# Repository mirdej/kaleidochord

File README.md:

# Kaleidochord
the kaleidochord (aka videoscheitholt or videozither) is a visual instrument that combines the videobass with the vmix

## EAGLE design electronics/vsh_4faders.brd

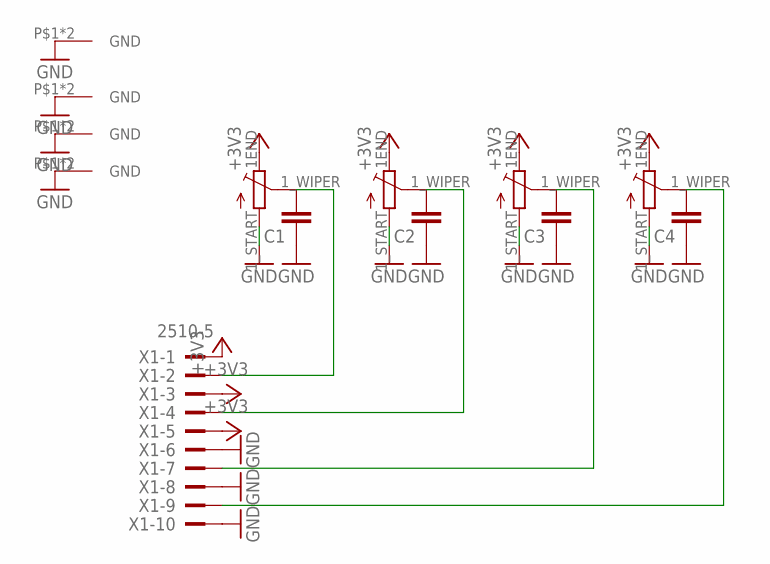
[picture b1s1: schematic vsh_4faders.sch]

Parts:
C1, C2, C3, C4: C-EUC0603; C0603
U$1, U$2, U$3, U$5: ALPS_FADER_MONO; ALPS_FADER_60MM_MONO
X1: 2510-5; PAK100/2500-5-10

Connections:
+3V3: U$1.1END (ENDE), U$2.1END (ENDE), U$3.1END (ENDE), U$5.1END (ENDE), X1.1, X1.3, X1.5
GND: C1.1, C2.1, C3.1, C4.1, U$1.1_START (ANFANG), U$1.P$1 (GND), U$1.P$2 (GND), U$2.1_START (ANFANG), U$2.P$1 (GND), U$2.P$2 (GND), U$3.1_START (ANFANG), U$3.P$1 (GND), U$3.P$2 (GND), U$5.1_START (ANFANG), U$5.P$1 (GND), U$5.P$2 (GND), X1.6, X1.8, X1.10
unnamed: C2.2, U$1.1_WIPER (SCHLEIFER), X1.4
unnamed: C1.2, U$5.1_WIPER (SCHLEIFER), X1.2
unnamed: C4.2, U$3.1_WIPER (SCHLEIFER), X1.9
unnamed: C3.2, U$2.1_WIPER (SCHLEIFER), X1.7

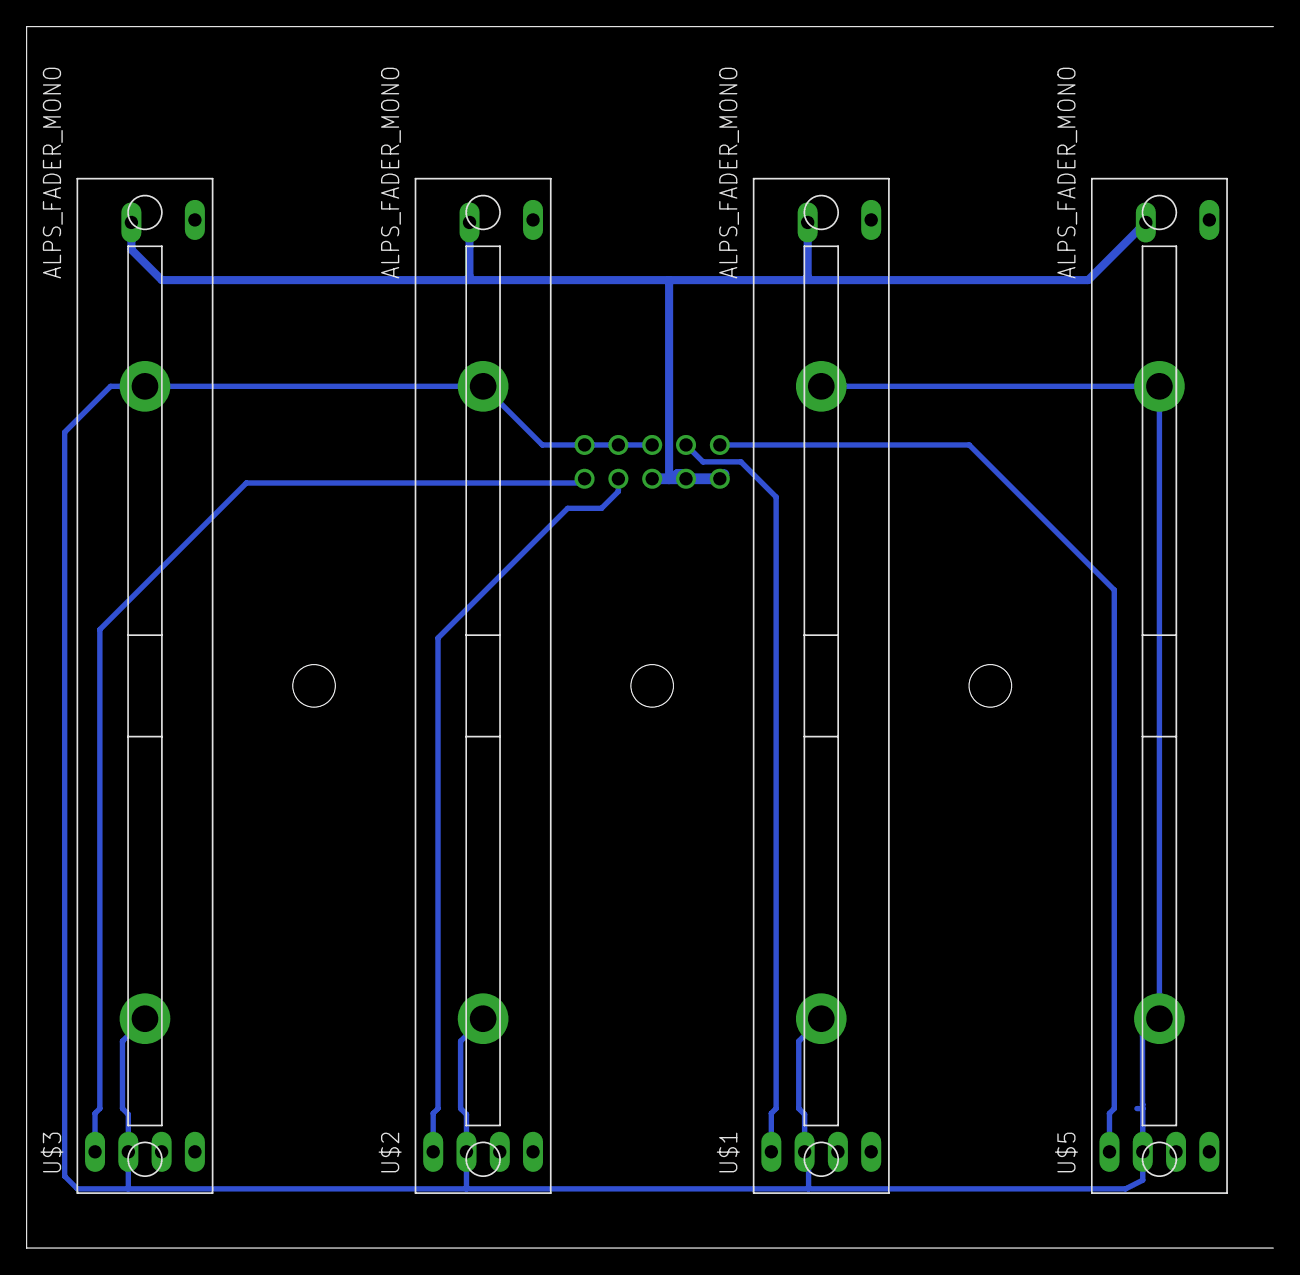
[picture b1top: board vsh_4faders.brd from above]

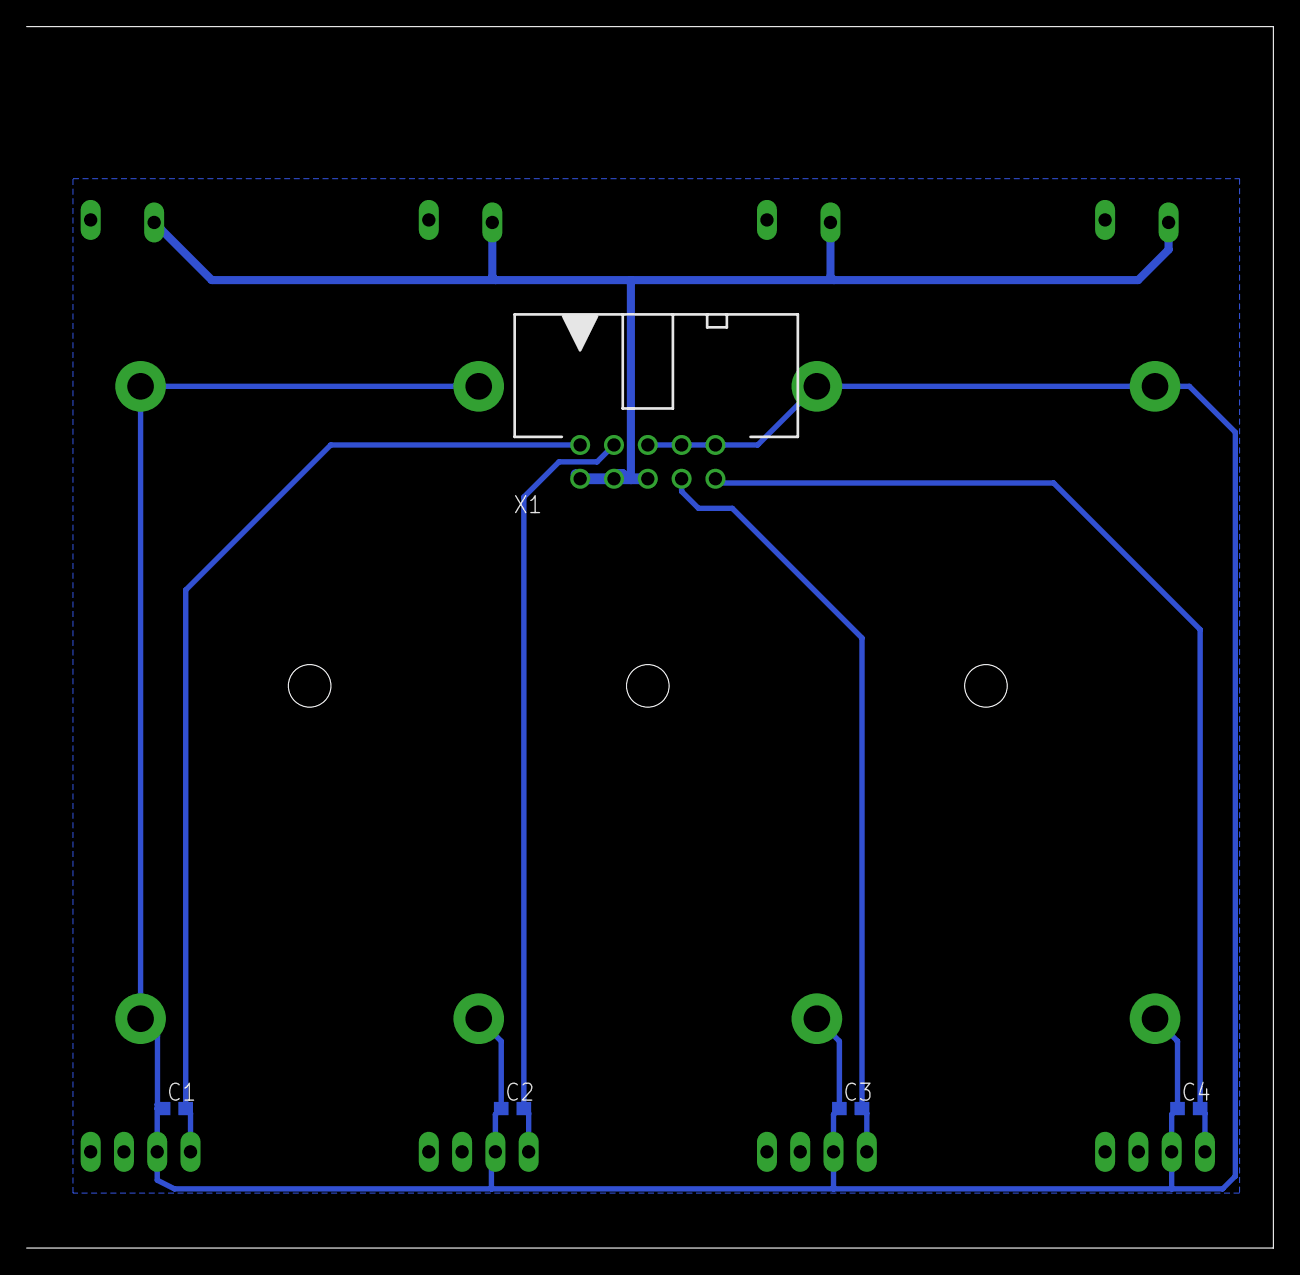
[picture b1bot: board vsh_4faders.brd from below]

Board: 2 copper layers, 93.6 x 91.7 mm, 9 parts (5 on the bottom side), 6 nets.

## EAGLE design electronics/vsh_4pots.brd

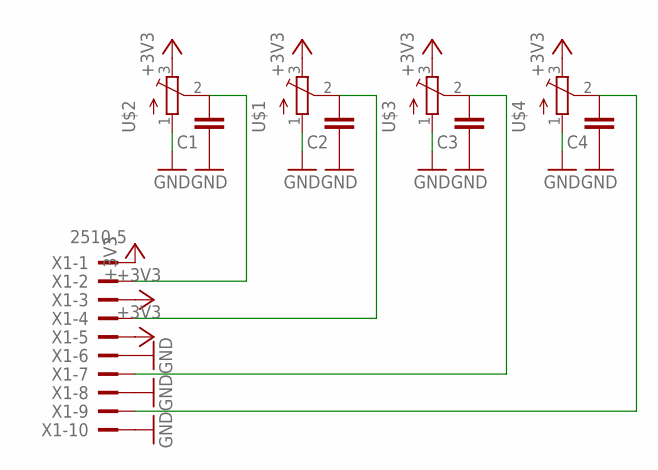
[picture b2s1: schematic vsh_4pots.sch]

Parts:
C1, C2, C3, C4: C-EUC0603; C0603
U$1, U$2, U$3, U$4: ALPS_RK09K111_H09L1120; ALPS_RK09L1120
X1: 2510-5; PAK100/2500-5-10

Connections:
+3V3: U$1.3 (E), U$2.3 (E), U$3.3 (E), U$4.3 (E), X1.1, X1.3, X1.5
GND: C1.1, C2.1, C3.1, C4.1, U$1.1 (S), U$2.1 (S), U$3.1 (S), U$4.1 (S), X1.6, X1.8, X1.10
unnamed: C2.2, U$1.2 (W), X1.4
unnamed: C1.2, U$2.2 (W), X1.2
unnamed: C4.2, U$4.2 (W), X1.9
unnamed: C3.2, U$3.2 (W), X1.7

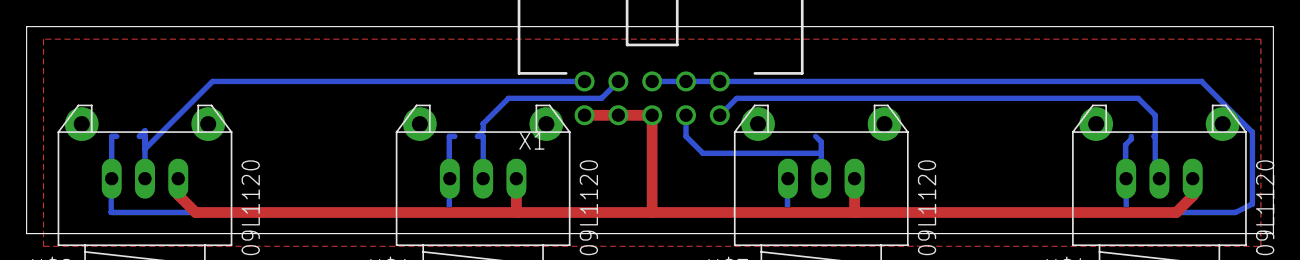
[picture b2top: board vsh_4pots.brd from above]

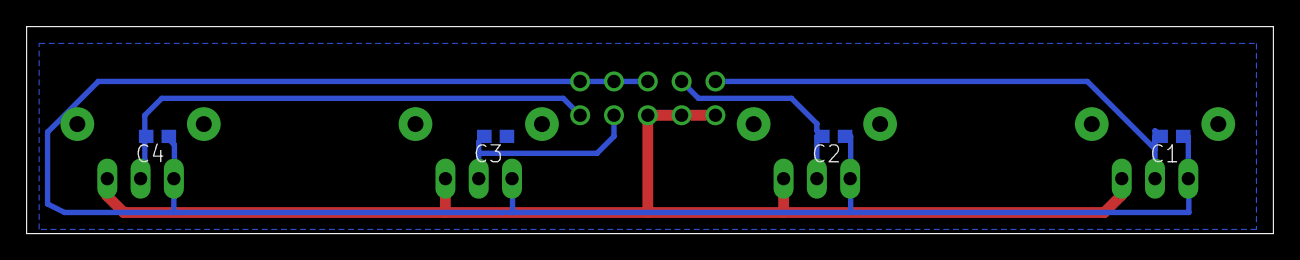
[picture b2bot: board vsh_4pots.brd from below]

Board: 2 copper layers, 93.6 x 15.5 mm, 9 parts (4 on the bottom side), 6 nets.

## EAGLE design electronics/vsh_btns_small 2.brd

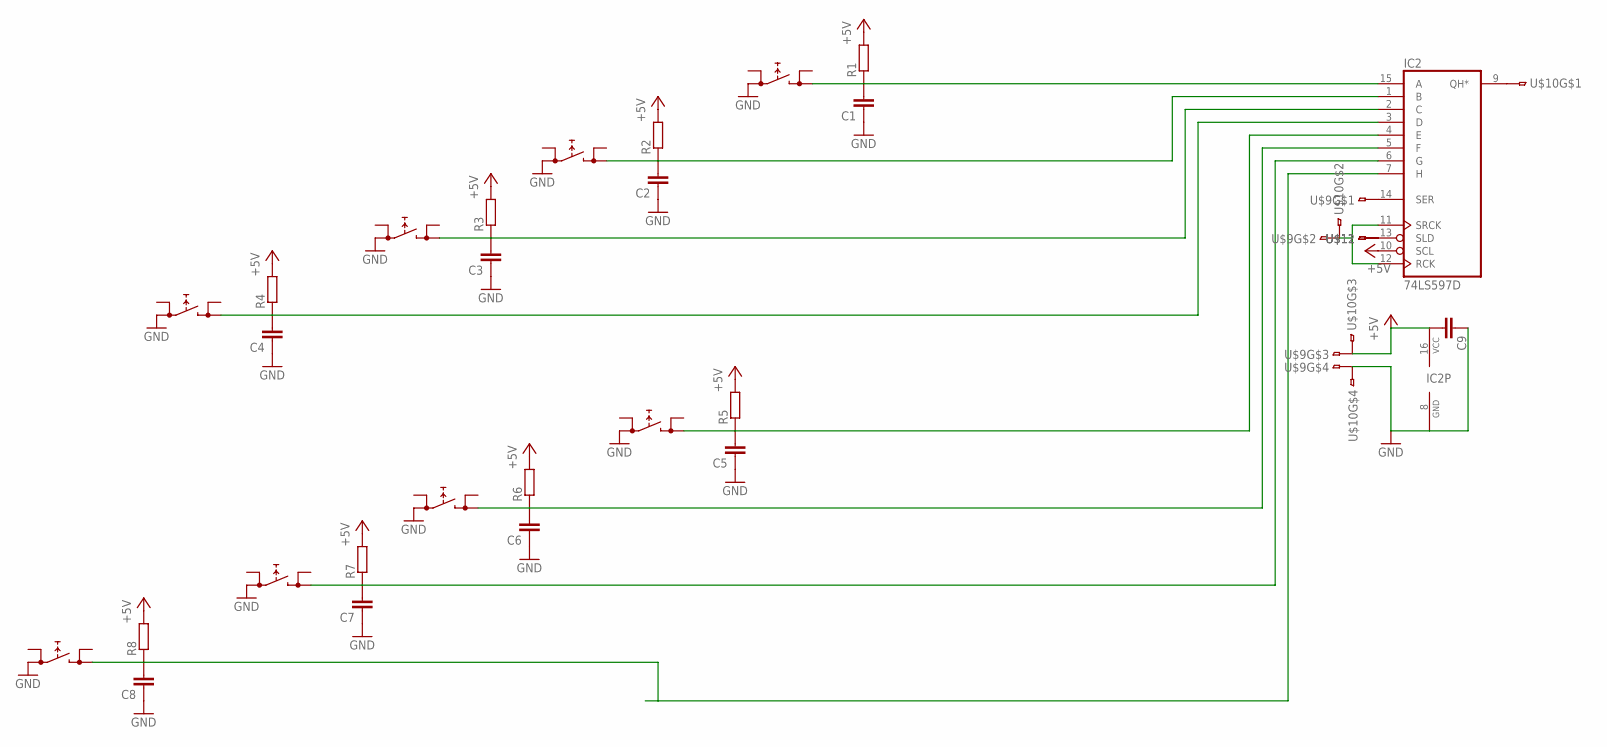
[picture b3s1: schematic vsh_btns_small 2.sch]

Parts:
C1, C2, C3, C4, C5, C6, C7, C8, C9: C-EUC1206; C1206
IC2: 74LS597D; SO16
R1, R2, R3, R4, R5, R6, R7, R8: R-EU_R1206; R1206
U$1, U$2, U$3, U$4, U$5, U$6, U$7, U$8: PRINTTASTER_SMDALPS-SKQ; SKQGAKE010
U$9, U$10: 4PIN-SMD; 4PIN-SMD-2.54
U$11, U$12: 1PINSMD

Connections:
+5V: C9.2, IC2.10 (SCL), IC2.16 (VCC), R1.2, R2.2, R3.2, R4.2, R5.2, R6.2, R7.2, R8.2, U$9.3, U$10.3
GND: C1.1, C2.1, C3.1, C4.1, C5.1, C6.1, C7.1, C8.1, C9.1, IC2.8 (GND), U$1.2 (0), U$2.2 (0), U$3.2 (0), U$4.2 (0), U$5.2 (0), U$6.2 (0), U$7.2 (0), U$8.2 (0), U$9.4, U$10.4
MISO: IC2.9 (QH*), U$10.1
unnamed: C1.2, IC2.15 (A), R1.1, U$1.4 (1)
unnamed: C2.2, IC2.1 (B), R2.1, U$2.4 (1)
unnamed: C3.2, IC2.2 (C), R3.1, U$3.4 (1)
unnamed: C4.2, IC2.3 (D), R4.1, U$4.4 (1)
unnamed: C5.2, IC2.4 (E), R5.1, U$5.4 (1)
unnamed: C6.2, IC2.5 (F), R6.1, U$6.4 (1)
unnamed: C7.2, IC2.6 (G), R7.1, U$7.4 (1)
unnamed: IC2.14 (SER), U$9.1
unnamed: IC2.11 (SRCK), IC2.12 (RCK), U$9.2, U$10.2
unnamed: C8.2, IC2.7 (H), R8.1, U$8.4 (1)
unnamed: IC2.13 (SLD), U$11.2, U$12.2

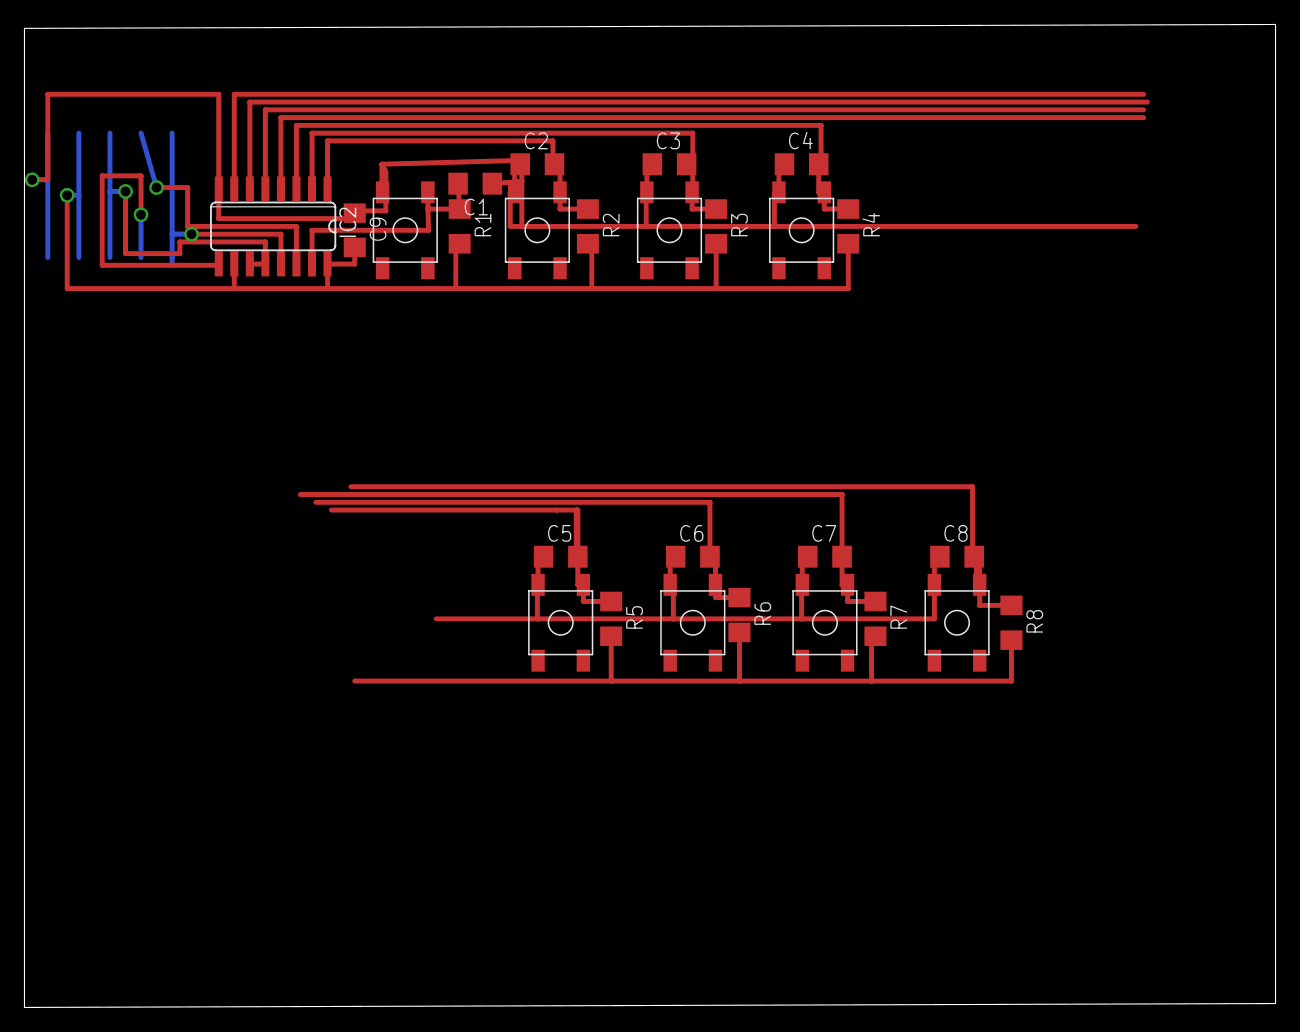
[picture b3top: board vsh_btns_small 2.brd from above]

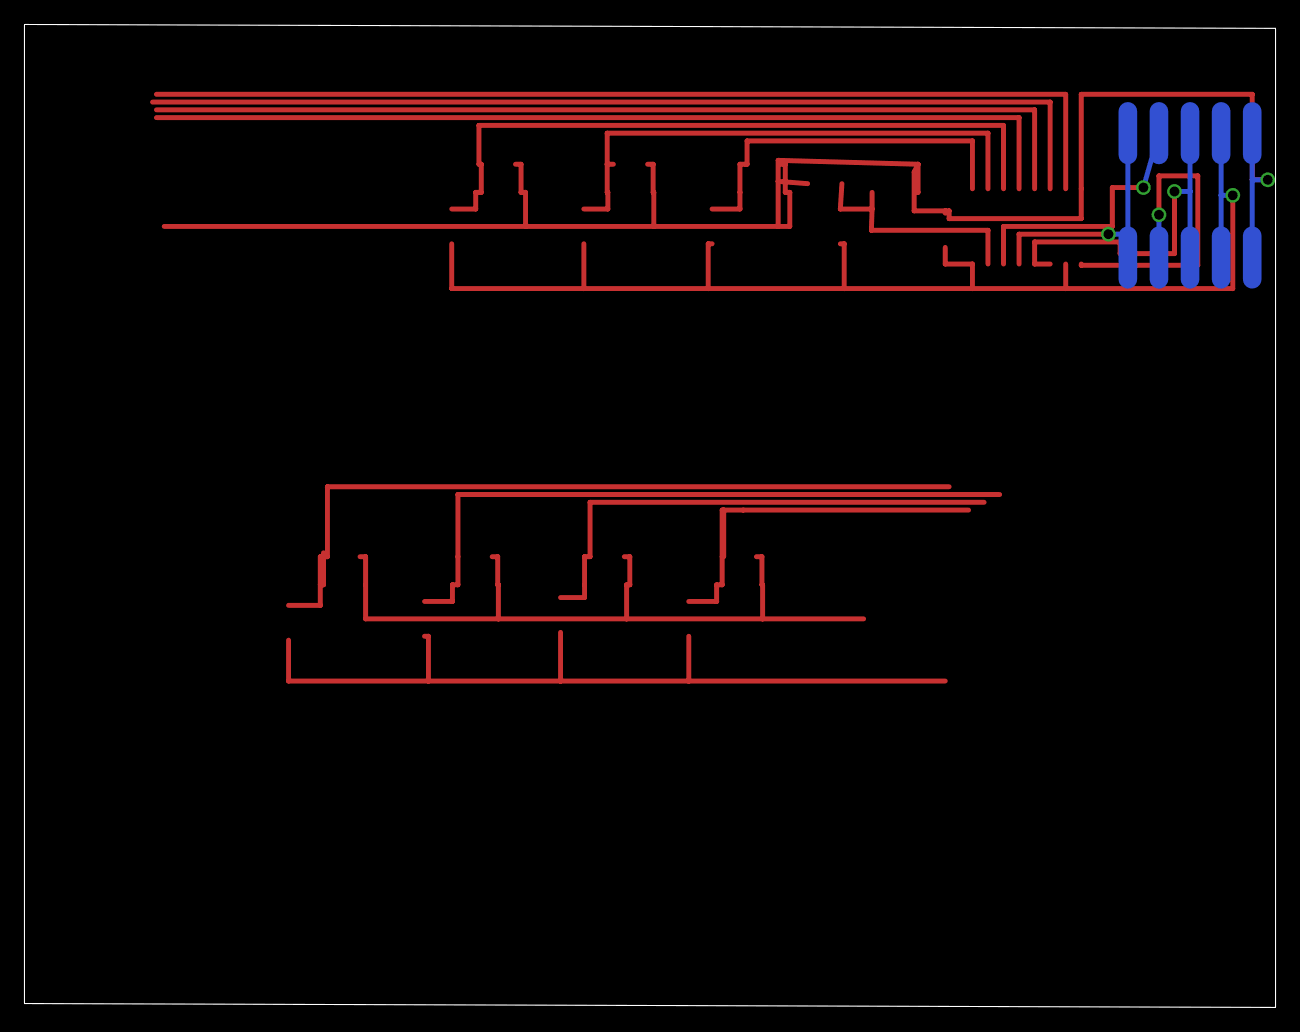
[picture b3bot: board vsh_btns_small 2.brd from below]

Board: 2 copper layers, 102.2 x 80.3 mm, 30 parts (4 on the bottom side), 14 nets.

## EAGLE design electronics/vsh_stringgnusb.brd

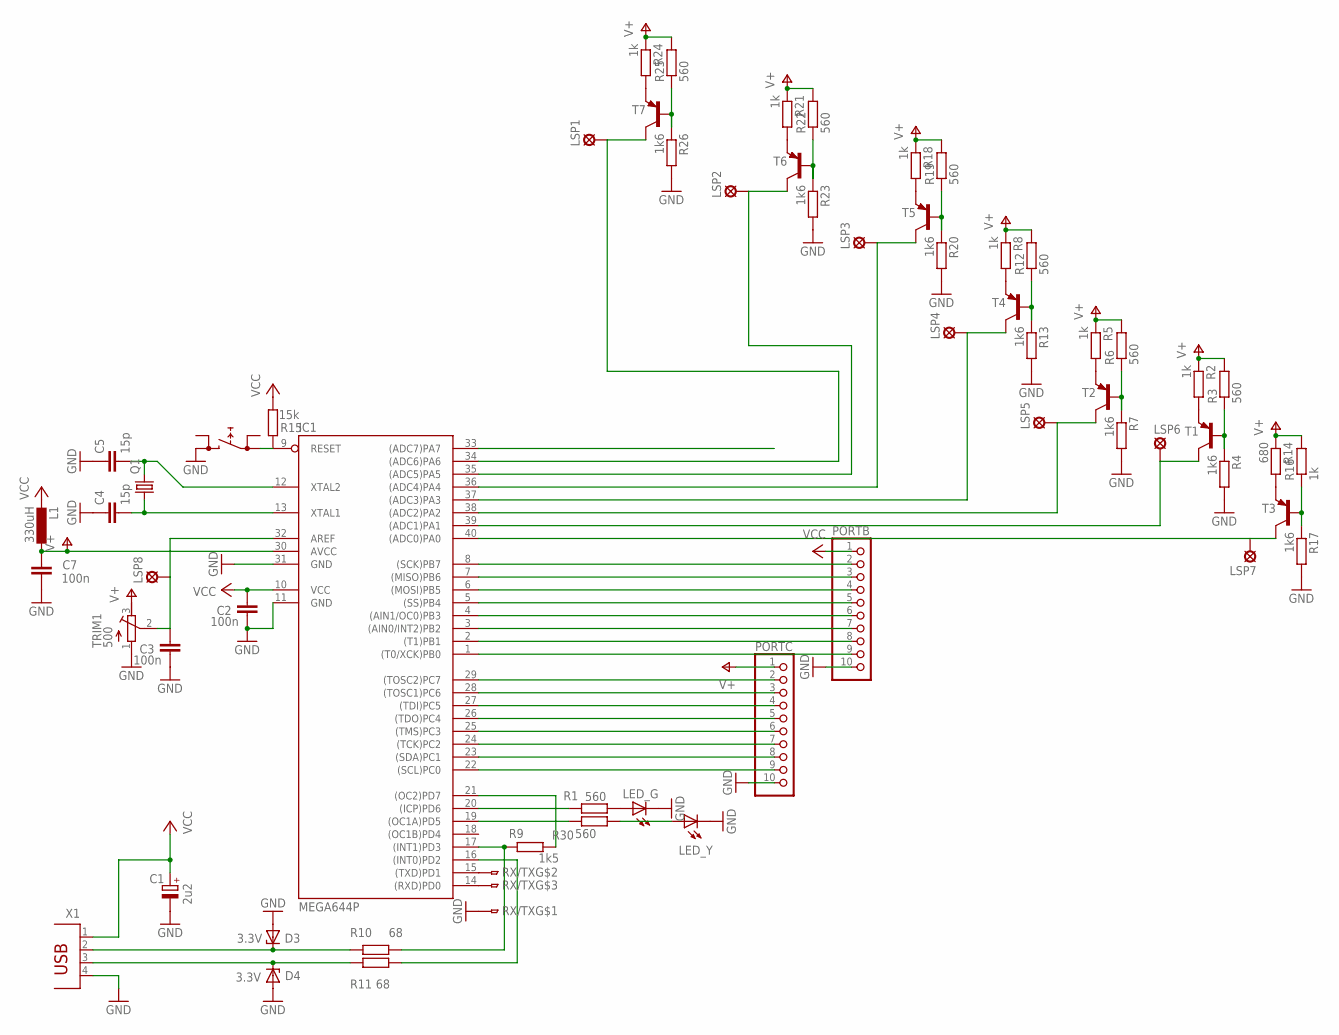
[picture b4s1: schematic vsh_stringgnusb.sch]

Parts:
C1: 2u2; CT3528
C2, C7: 100n; C0805
C3: 100n; C1206
C4, C5: 15p; C1206
D3, D4: 3.3V; SOD80C
IC1: MEGA644P; DIL40
L1: 330uH; L1812
LED_G: LEDCHIPLED_1206; CHIPLED_1206
LED_Y: LEDCHIPLED_1206; CHIPLED_1206
LSP1, LSP2, LSP3, LSP4, LSP5, LSP6, LSP7, LSP8: LSP11
PORTB: 10-PIN-SMD-2.54; 10PIN-SMD-2.54
PORTC: 10-PIN-SMD-2.54; 10PIN-SMD-2.54
Q1: CRYSTALHC49UP; HC49UP
R1, R30: 560; M1206
R2, R5, R8, R16, R18, R21, R24: 1k; R1206
R3, R6, R12, R19, R22, R25: 560; R1206
R4, R7, R13, R17, R20, R23, R26: 1k6; R1206
R9: 1k5; M1206
R10, R11: 68; M1206
R14: 680; R1206
R15: 15k; M1206
RESET: PRINTTASTER_SMD; SMD_SWITCH
RX/TX: 3PIN-SMD-2.54
T1, T2, T3, T4, T5, T6, T7: -PNP-SOT23-BCE; SOT23-BCE
TRIM1: 500; RTRIM64Y
X1: PN61729

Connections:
D+: D4.C, R11.1, X1.3
D-: D3.C, R10.1, X1.2
GND: C1.-, C2.2, C3.2, C4.1, C5.1, C7.2, D3.A, D4.A, IC1.11 (GND), IC1.31 (GND), LED_G.C, LED_Y.C, PORTB.10, PORTC.10, R4.2, R7.2, R13.2, R17.2, R20.2, R23.2, R26.2, RESET.BB (1), RX/TX.1, TRIM1.1 (E), X1.4
MISO: IC1.7 ((MISO)PB6), PORTB.3
MOSI: IC1.6 ((MOSI)PB5), PORTB.4
unnamed: IC1.17 ((INT1)PD3), R9.2, R10.2
unnamed: IC1.9 (RESET), R15.1, RESET.AA (0)
unnamed: IC1.15 ((TXD)PD1), RX/TX.2
unnamed: IC1.14 ((RXD)PD0), RX/TX.3
unnamed: LED_G.A, R1.2
unnamed: C4.2, IC1.13 (XTAL1), Q1.1
unnamed: IC1.20 ((ICP)PD6), R1.1
unnamed: IC1.19 ((OC1A)PD5), R30.1
unnamed: LED_Y.A, R30.2
unnamed: R14.2, T3.E
unnamed: C3.1, IC1.32 (AREF), LSP8.MP, TRIM1.2 (S)
unnamed: IC1.21 ((OC2)PD7), R9.1
unnamed: R2.2, T1.E
unnamed: IC1.35 ((ADC5)PA5), LSP2.MP, T6.C
unnamed: IC1.37 ((ADC3)PA3), LSP4.MP, T4.C
unnamed: IC1.38 ((ADC2)PA2), LSP5.MP, T2.C
unnamed: IC1.40 ((ADC0)PA0), LSP7.MP, T3.C
unnamed: R16.1, R17.1, T3.B
unnamed: IC1.4 ((AIN1/OC0)PB3), PORTB.6
unnamed: IC1.3 ((AIN0/INT2)PB2), PORTB.7
unnamed: IC1.2 ((T1)PB1), PORTB.8
unnamed: IC1.1 ((T0/XCK)PB0), PORTB.9
unnamed: IC1.16 ((INT0)PD2), R11.2
unnamed: IC1.29 ((TOSC2)PC7), PORTC.2
unnamed: IC1.28 ((TOSC1)PC6), PORTC.3
unnamed: IC1.27 ((TDI)PC5), PORTC.4
unnamed: IC1.26 ((TDO)PC4), PORTC.5
unnamed: IC1.25 ((TMS)PC3), PORTC.6
unnamed: IC1.24 ((TCK)PC2), PORTC.7
unnamed: IC1.23 ((SDA)PC1), PORTC.8
unnamed: IC1.22 ((SCL)PC0), PORTC.9
unnamed: IC1.39 ((ADC1)PA1), LSP6.MP, T1.C
unnamed: R3.1, R4.1, T1.B
unnamed: C5.2, IC1.12 (XTAL2), Q1.2
unnamed: R5.2, T2.E
unnamed: R6.1, R7.1, T2.B
unnamed: R8.2, T4.E
unnamed: R12.1, R13.1, T4.B
unnamed: R18.2, T5.E
unnamed: IC1.36 ((ADC4)PA4), LSP3.MP, T5.C
unnamed: R19.1, R20.1, T5.B
unnamed: R21.2, T6.E
unnamed: R22.1, R23.1, T6.B
unnamed: R24.2, T7.E
unnamed: IC1.34 ((ADC6)PA6), LSP1.MP, T7.C
unnamed: R25.1, R26.1, T7.B
SCK: IC1.8 ((SCK)PB7), PORTB.2
SS: IC1.5 ((SS)PB4), PORTB.5
V+: C7.1, IC1.30 (AVCC), L1.1, PORTC.1, R2.1, R3.2, R5.1, R6.2, R8.1, R12.2, R14.1, R16.2, R18.1, R19.2, R21.1, R22.2, R24.1, R25.2, TRIM1.3 (A)
VCC: C1.+, C2.1, IC1.10 (VCC), L1.2, PORTB.1, R15.2, X1.1

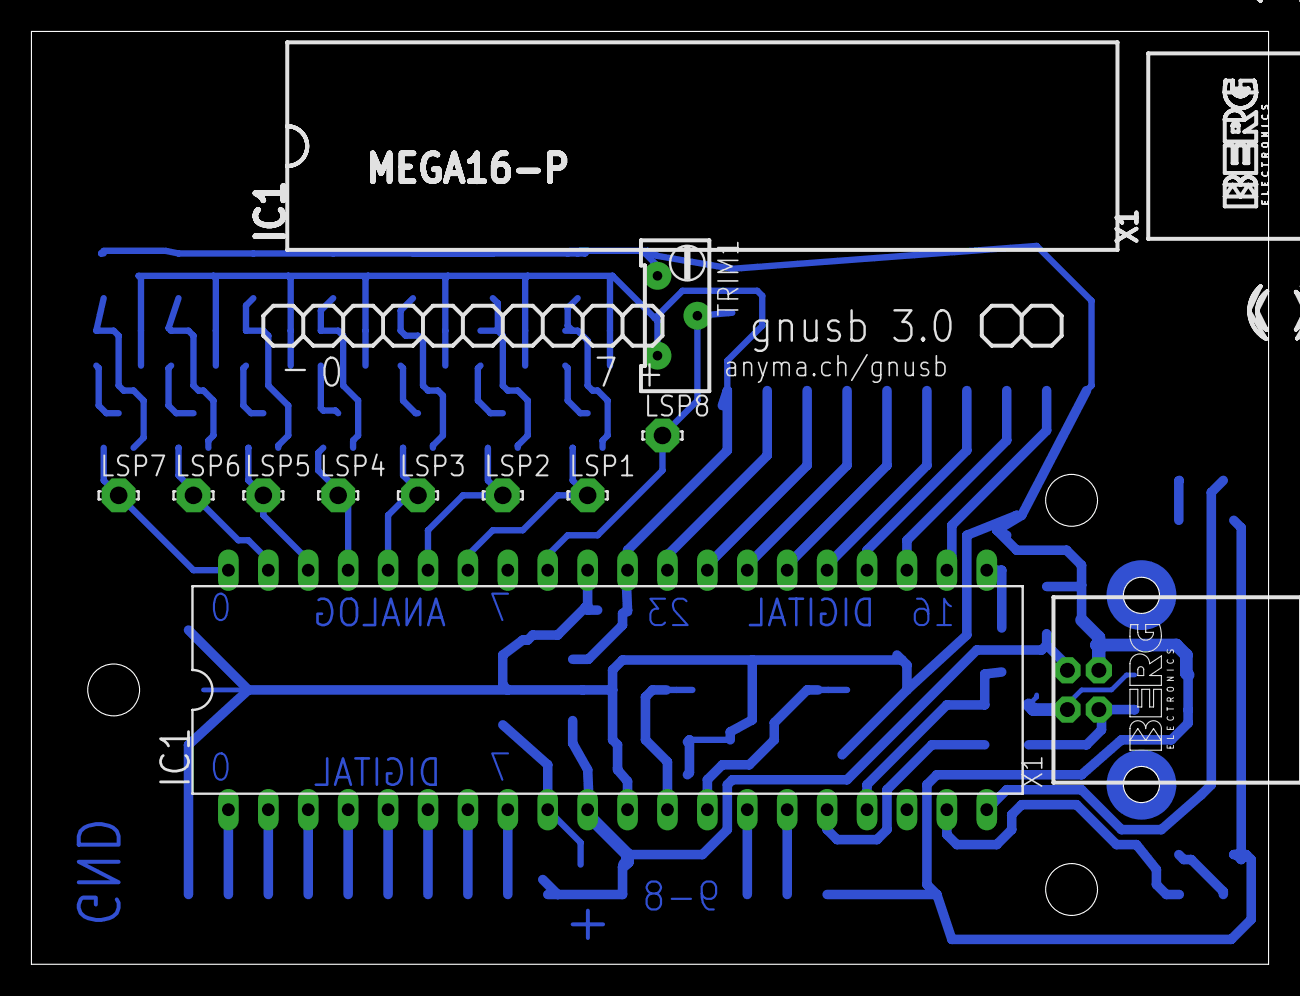
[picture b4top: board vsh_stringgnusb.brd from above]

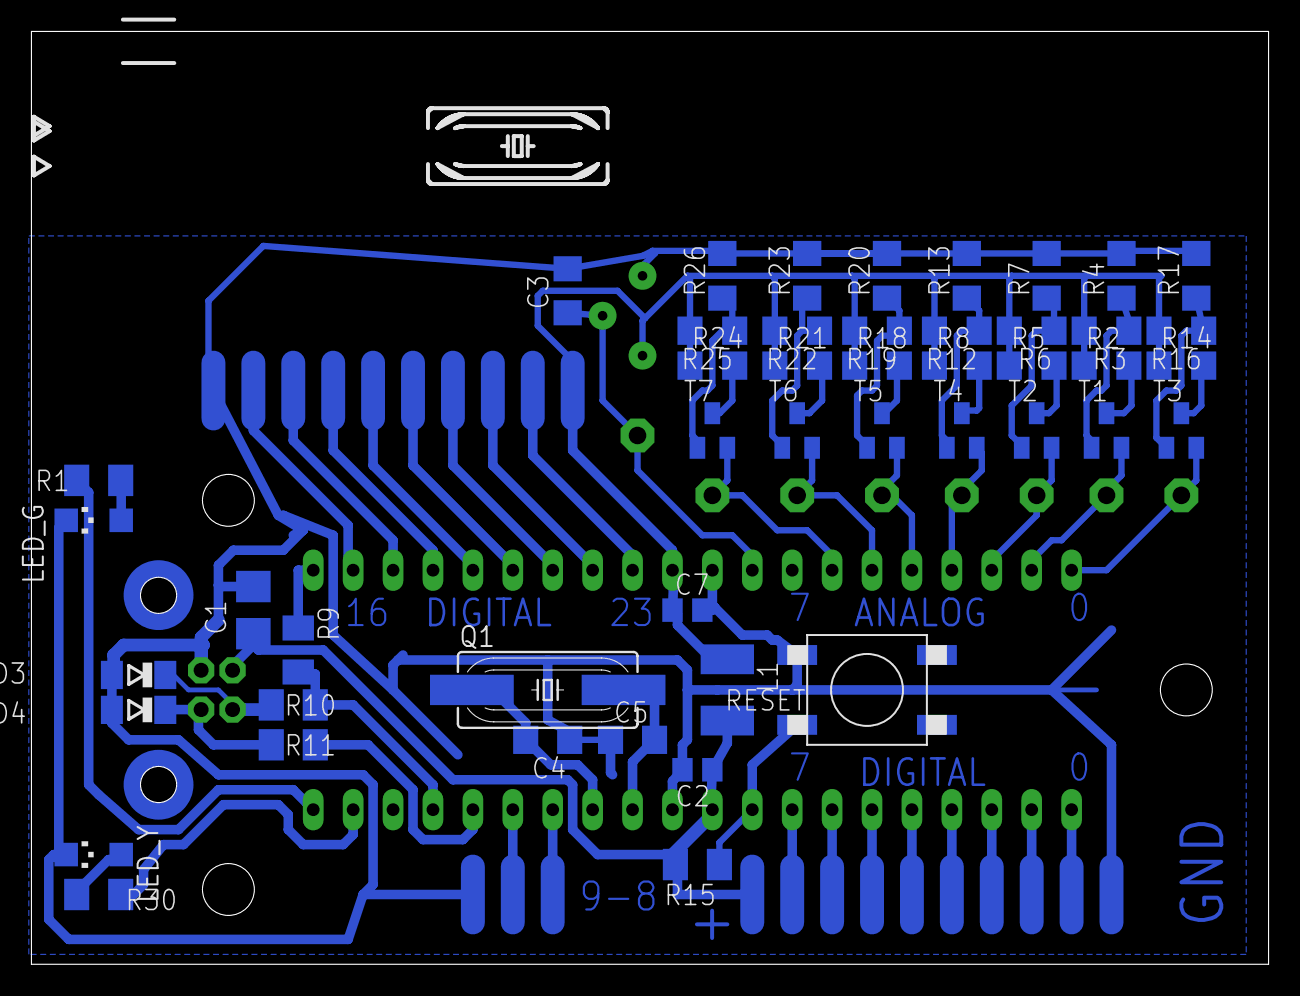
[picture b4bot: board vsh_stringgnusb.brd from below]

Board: 2 copper layers, 78.7 x 59.4 mm, 61 parts (50 on the bottom side), 55 nets.

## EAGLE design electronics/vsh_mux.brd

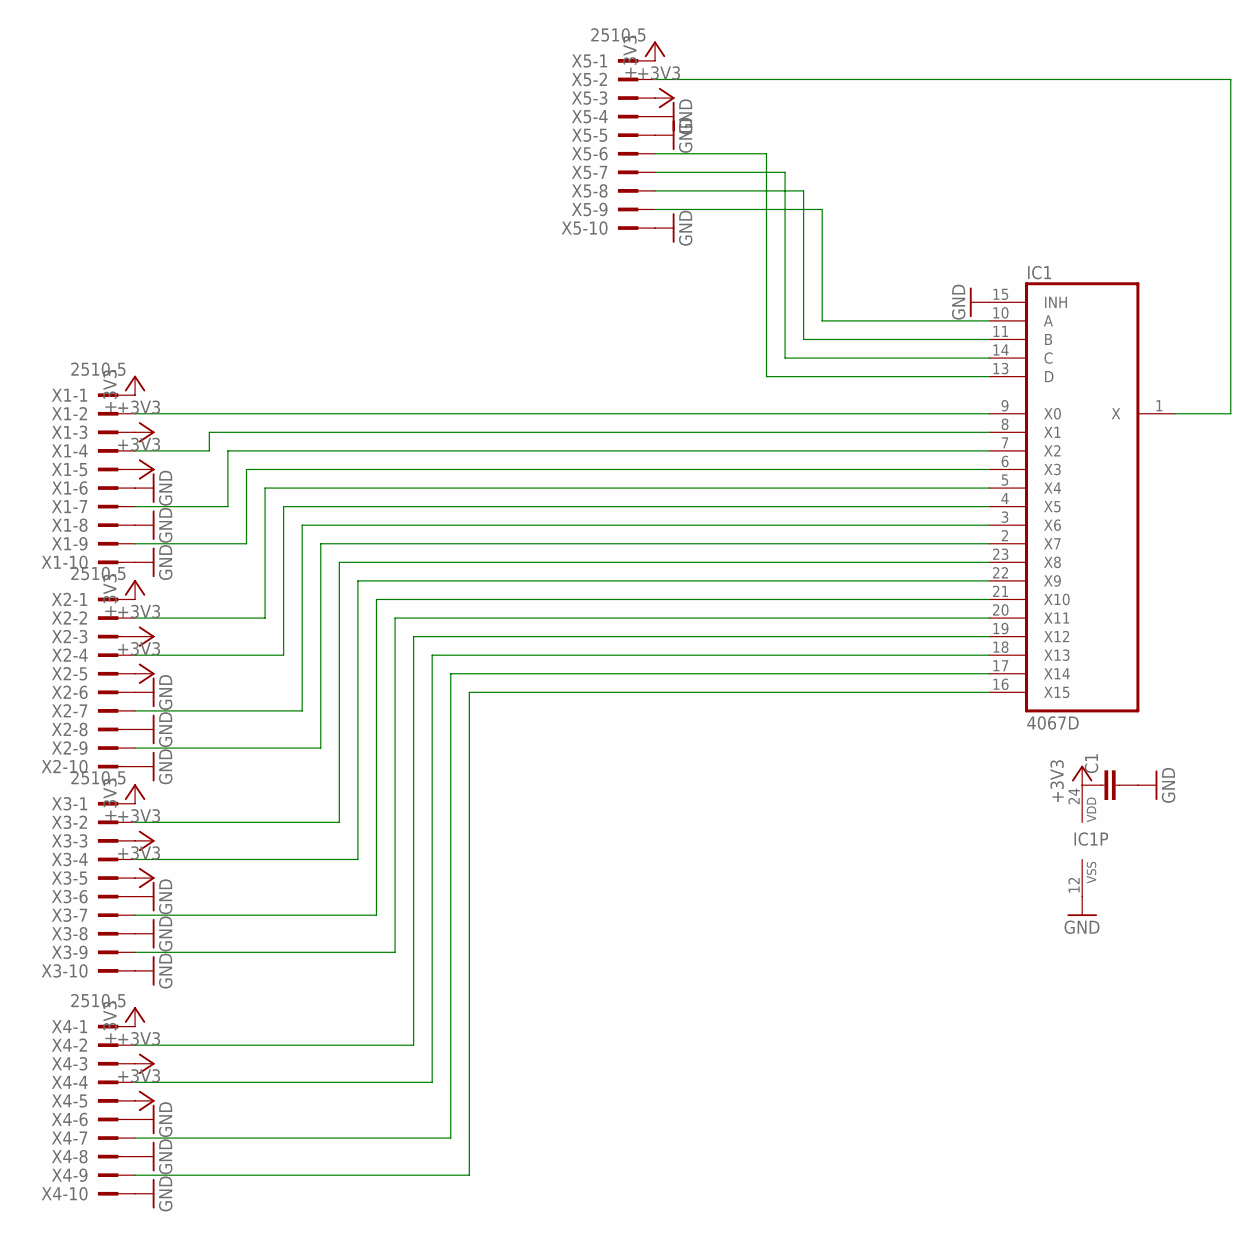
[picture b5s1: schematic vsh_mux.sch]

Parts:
C1: C-EUC1206; C1206
IC1: 4067D; SO24W
X1, X2, X3, X4, X5: 2510-5; PAK100/2500-5-10

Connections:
+3V3: C1.1, IC1.24 (VDD), X1.1, X1.3, X1.5, X2.1, X2.3, X2.5, X3.1, X3.3, X3.5, X4.1, X4.3, X4.5, X5.1, X5.3
GND: C1.2, IC1.12 (VSS), IC1.15 (INH), X1.6, X1.8, X1.10, X2.6, X2.8, X2.10, X3.6, X3.8, X3.10, X4.6, X4.8, X4.10, X5.4, X5.5, X5.10
unnamed: IC1.4 (X5), X2.4
unnamed: IC1.8 (X1), X1.4
unnamed: IC1.1 (X), X5.2
unnamed: IC1.9 (X0), X1.2
unnamed: IC1.6 (X3), X1.9
unnamed: IC1.2 (X7), X2.9
unnamed: IC1.7 (X2), X1.7
unnamed: IC1.3 (X6), X2.7
unnamed: IC1.22 (X9), X3.4
unnamed: IC1.23 (X8), X3.2
unnamed: IC1.20 (X11), X3.9
unnamed: IC1.21 (X10), X3.7
unnamed: IC1.18 (X13), X4.4
unnamed: IC1.10 (A), X5.9
unnamed: IC1.16 (X15), X4.9
unnamed: IC1.17 (X14), X4.7
unnamed: IC1.5 (X4), X2.2
unnamed: IC1.19 (X12), X4.2
unnamed: IC1.11 (B), X5.8
unnamed: IC1.13 (D), X5.6
unnamed: IC1.14 (C), X5.7

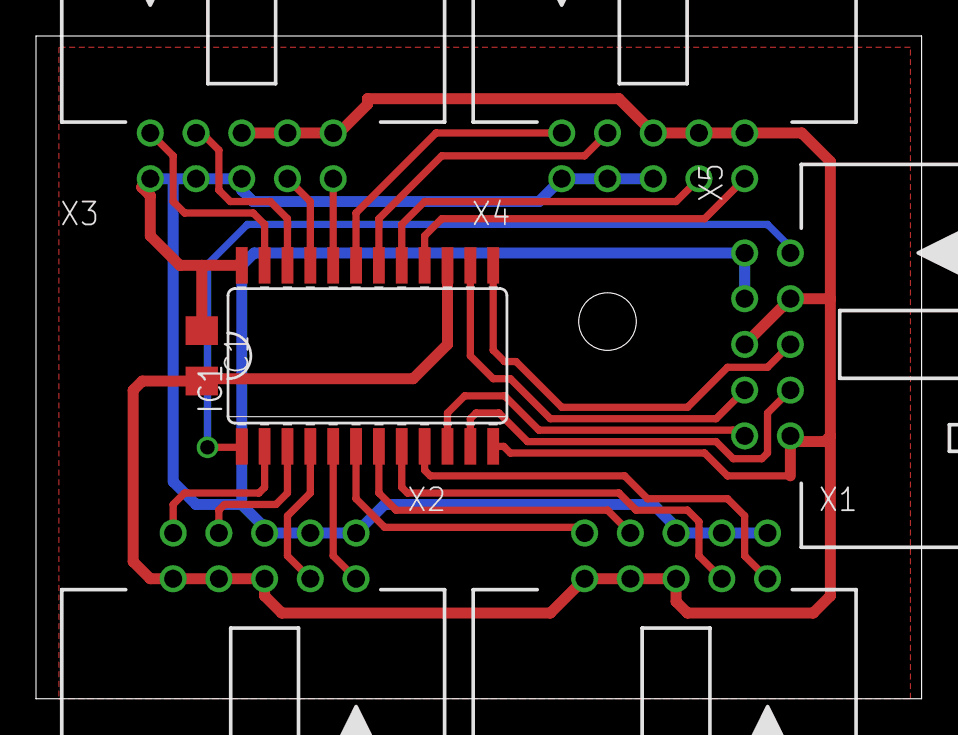
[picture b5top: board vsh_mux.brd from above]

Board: 2 copper layers, 49.2 x 36.8 mm, 7 parts (0 on the bottom side), 23 nets.

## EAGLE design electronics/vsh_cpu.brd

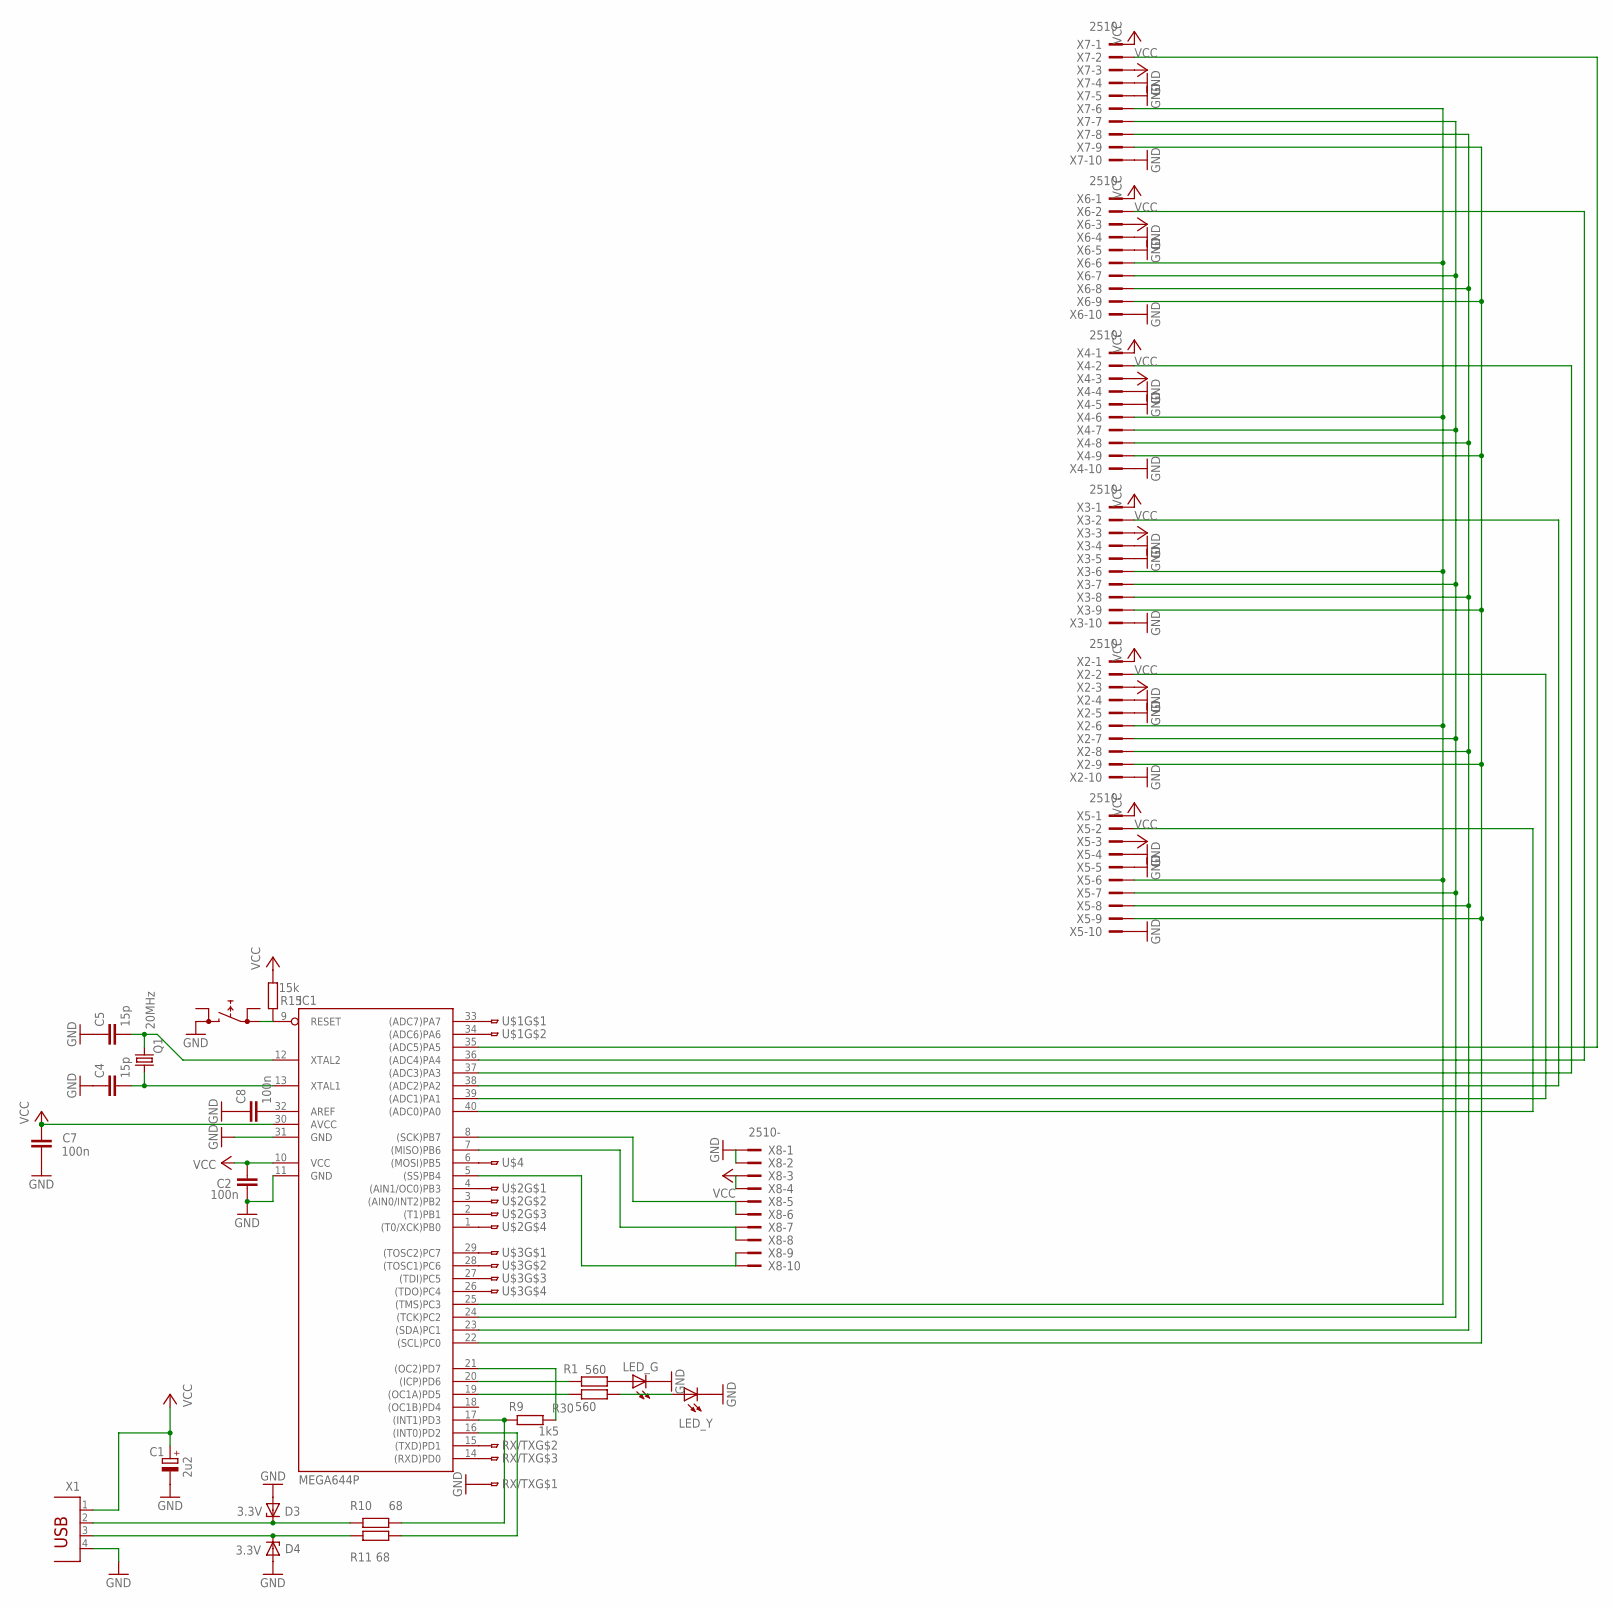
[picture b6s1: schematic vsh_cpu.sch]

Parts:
C1: 2u2; CT3528
C2, C7, C8: 100n; C0805
C4, C5: 15p; C1206
D3, D4: 3.3V; SOD80C
IC1: MEGA644P; DIL40
LED_G: LEDCHIPLED_1206; CHIPLED_1206
LED_Y: LEDCHIPLED_1206; CHIPLED_1206
Q1: 20MHz; HC49UP
R1, R30: 560; M1206
R9: 1k5; M1206
R10, R11: 68; M1206
R15: 15k; M1206
RESET: PRINTTASTER_SMD; SMD_SWITCH
RX/TX: 3PIN-SMD-2.54
U$1: 2PIN-SMD-2.54
U$2, U$3: 4PIN-SMD; 4PIN-SMD-2.54
U$4: 1PINSMD
X1: PN61729
X2, X3, X4, X5, X6, X7, X8: 2510-; PAK100/2500-10

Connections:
D+: D4.C, R11.1, X1.3
D-: D3.C, R10.1, X1.2
GND: C1.-, C2.2, C4.1, C5.1, C7.2, C8.1, D3.A, D4.A, IC1.11 (GND), IC1.31 (GND), LED_G.C, LED_Y.C, RESET.BB (1), RX/TX.1, X1.4, X2.4, X2.5, X2.10, X3.4, X3.5, X3.10, X4.4, X4.5, X4.10, X5.4, X5.5, X5.10, X6.4, X6.5, X6.10, X7.4, X7.5, X7.10, X8.1, X8.2
unnamed: IC1.17 ((INT1)PD3), R9.2, R10.2
unnamed: IC1.9 (RESET), R15.1, RESET.AA (0)
unnamed: IC1.15 ((TXD)PD1), RX/TX.2
unnamed: IC1.14 ((RXD)PD0), RX/TX.3
unnamed: LED_G.A, R1.2
unnamed: C4.2, IC1.13 (XTAL1), Q1.1
unnamed: IC1.20 ((ICP)PD6), R1.1
unnamed: IC1.19 ((OC1A)PD5), R30.1
unnamed: LED_Y.A, R30.2
unnamed: IC1.40 ((ADC0)PA0), X5.2
unnamed: C8.2, IC1.32 (AREF)
unnamed: IC1.39 ((ADC1)PA1), X2.2
unnamed: IC1.21 ((OC2)PD7), R9.1
unnamed: IC1.38 ((ADC2)PA2), X3.2
unnamed: IC1.25 ((TMS)PC3), X2.6, X3.6, X4.6, X5.6, X6.6, X7.6
unnamed: IC1.33 ((ADC7)PA7), U$1.2
unnamed: IC1.24 ((TCK)PC2), X2.7, X3.7, X4.7, X5.7, X6.7, X7.7
unnamed: IC1.34 ((ADC6)PA6), U$1.3
unnamed: IC1.23 ((SDA)PC1), X2.8, X3.8, X4.8, X5.8, X6.8, X7.8
unnamed: IC1.8 ((SCK)PB7), X8.5, X8.6
unnamed: IC1.37 ((ADC3)PA3), X4.2
unnamed: IC1.36 ((ADC4)PA4), X6.2
unnamed: IC1.7 ((MISO)PB6), X8.7, X8.8
unnamed: IC1.5 ((SS)PB4), X8.9, X8.10
unnamed: IC1.16 ((INT0)PD2), R11.2
unnamed: IC1.22 ((SCL)PC0), X2.9, X3.9, X4.9, X5.9, X6.9, X7.9
unnamed: IC1.35 ((ADC5)PA5), X7.2
unnamed: IC1.4 ((AIN1/OC0)PB3), U$2.1
unnamed: IC1.3 ((AIN0/INT2)PB2), U$2.2
unnamed: IC1.2 ((T1)PB1), U$2.3
unnamed: IC1.29 ((TOSC2)PC7), U$3.1
unnamed: IC1.28 ((TOSC1)PC6), U$3.2
unnamed: IC1.27 ((TDI)PC5), U$3.3
unnamed: IC1.26 ((TDO)PC4), U$3.4
unnamed: C5.2, IC1.12 (XTAL2), Q1.2
unnamed: IC1.1 ((T0/XCK)PB0), U$2.4
unnamed: IC1.6 ((MOSI)PB5), U$4.2
VCC: C1.+, C2.1, C7.1, IC1.10 (VCC), IC1.30 (AVCC), R15.2, X1.1, X2.1, X2.3, X3.1, X3.3, X4.1, X4.3, X5.1, X5.3, X6.1, X6.3, X7.1, X7.3, X8.3, X8.4
